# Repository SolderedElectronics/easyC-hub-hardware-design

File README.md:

# easyC Hub Hardware design

## About the product

|  |
| :----------------------------------------------------------: |
|      [Buy easyC Hub](https://www.solde.red/333018)      |

We made the easyC system for faster prototyping and easy connection between the components. However, some of the components have only one easyC port or you just want your cable managmenet made better. What to do in those cases? The easyC hub comes to the rescue! It has six connectors so you can easily expand your circuit. It’s as simple of a device as it can get.

## Repository contents

All Soldered Electronics hardware designed in KiCAD, and repositories are organized in the following way:

- CAD folder - contains KiCAD files (Schematics, Board, Panel Board), sorted by version. Change log lists all changes between versions.
- OUTPUTS - contains useful files, such as Bill of Materials (BOM), PDF of schematics, 3D .step file of the board and gerber files, sorted by version. 
- OUTPUTS -> Compliance - Certificates and useful legal stuff. 

## Want to contribute?

Please feel free to submit a pull request if you have any contributions. We encourage you to submit an issue or pull request if you find a bug. 

## About Soldered

At Soldered, we design and manufacture a wide selection of electronic products to help you turn your ideas into acts and bring you one step closer to your final project. Our products are intented for makers and crafted in-house by our experienced team in Osijek, Croatia. We believe that sharing is a crucial element for improvement and innovation, and we work hard to stay connected with all our makers regardless of their skill or experience level. Therefore, all our products are open-source. Finally, we always have your back. If you face any problem concerning either your shopping experience or your electronics project, our team will help you deal with it, offering efficient customer service and cost-free technical support anytime. Some of those might be useful for you:

- [Web Store](https://www.soldered.com/shop)
- [Tutorials & Projects](https://soldered.com/learn)
- [Community & Technical support](https://soldered.com/community)

## License info

All Soldered open-source hardware (OSH) is under The TAPR Open Hardware License. Read more in the LICENSE file. 

No warranty - all designs in this repository are distributed in the hope that they will be useful, but without any warranty. They are provided "AS IS", therefore without warranty of any kind, either expressed or implied. The entire quality and performance of what you do with the contents of this repository are your responsibility. In no event, Soldered Electronics will be liable for your damages, losses, including any general, special, incidental or consequential damage arising out of the use or inability to use the contents of this repository. 

## Have fun! 
And thank you from your fellow makers at Soldered Electronics.

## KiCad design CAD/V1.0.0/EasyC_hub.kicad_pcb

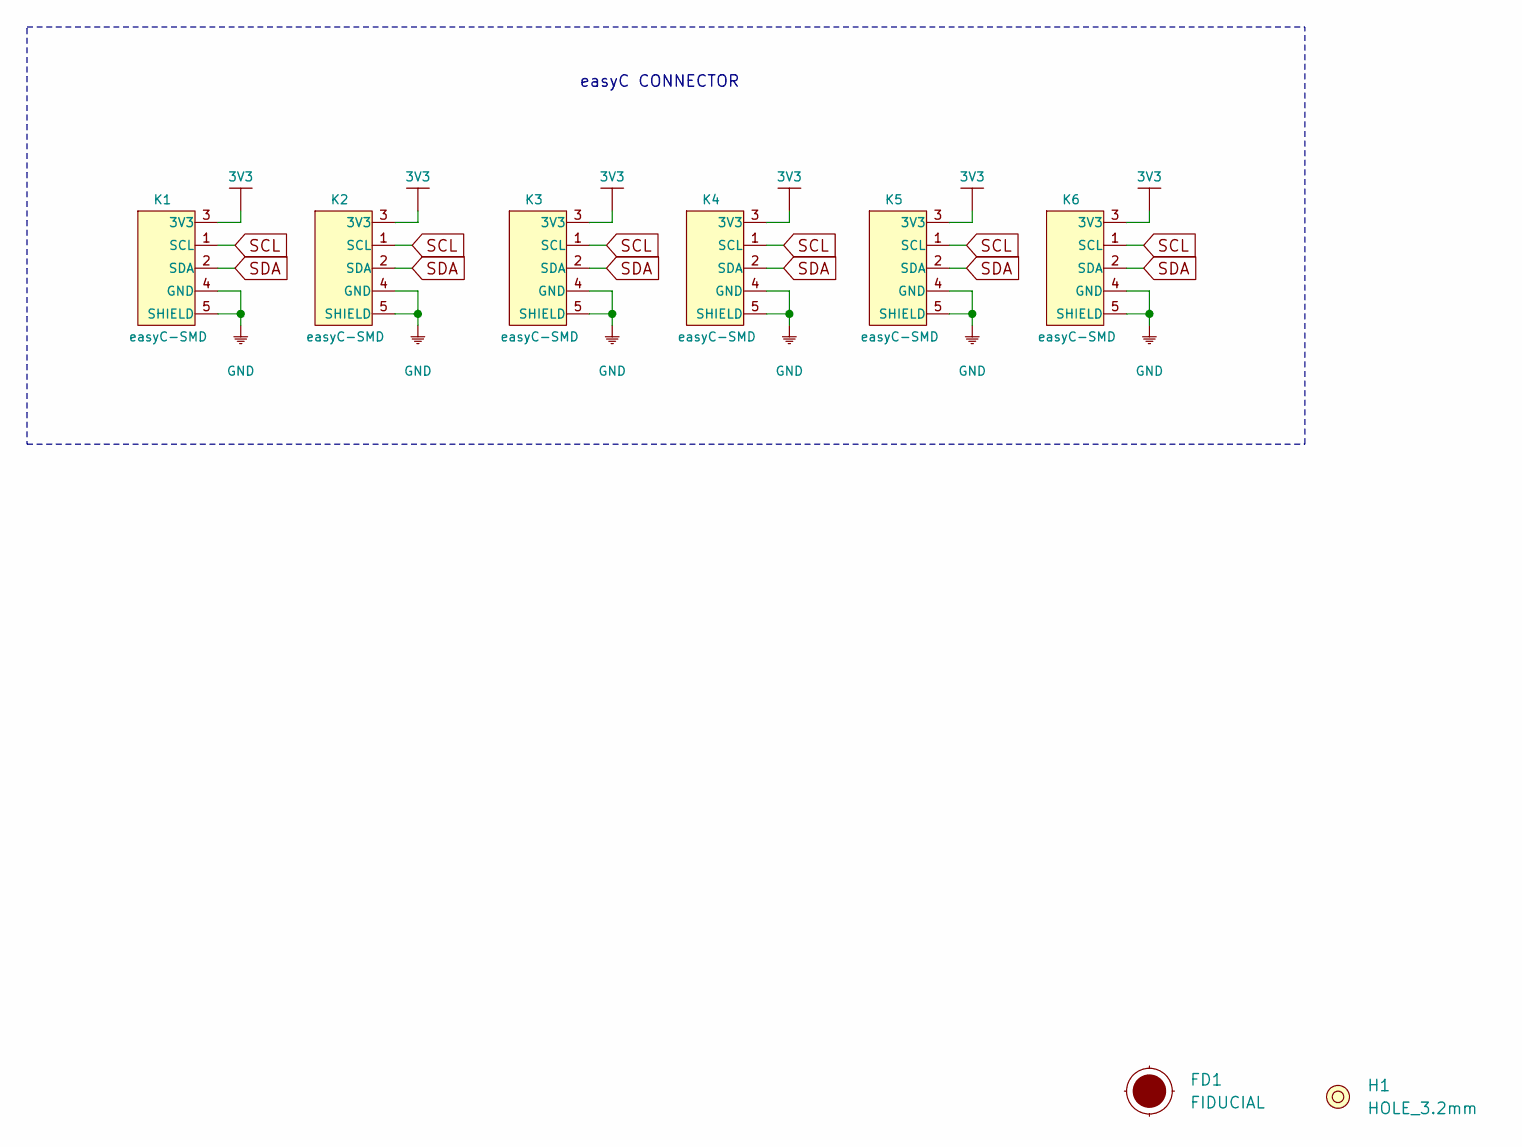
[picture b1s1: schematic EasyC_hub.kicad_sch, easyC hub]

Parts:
FD1: FIDUCIAL; FIDUCIAL_23
H1: HOLE_3.2mm
K1, K2, K3, K4, K5, K6: easyC-SMD; easyC-connector

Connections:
3V3: K1.3 (3V3), K2.3 (3V3), K3.3 (3V3), K4.3 (3V3), K5.3 (3V3), K6.3 (3V3)
GND: K1.4 (GND), K1.5 (SHIELD), K2.4 (GND), K2.5 (SHIELD), K3.4 (GND), K3.5 (SHIELD), K4.4 (GND), K4.5 (SHIELD), K5.4 (GND), K5.5 (SHIELD), K6.4 (GND), K6.5 (SHIELD)
SCL: K1.1 (SCL), K2.1 (SCL), K3.1 (SCL), K4.1 (SCL), K5.1 (SCL), K6.1 (SCL)
SDA: K1.2 (SDA), K2.2 (SDA), K3.2 (SDA), K4.2 (SDA), K5.2 (SDA), K6.2 (SDA)

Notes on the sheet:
easyC CONNECTOR

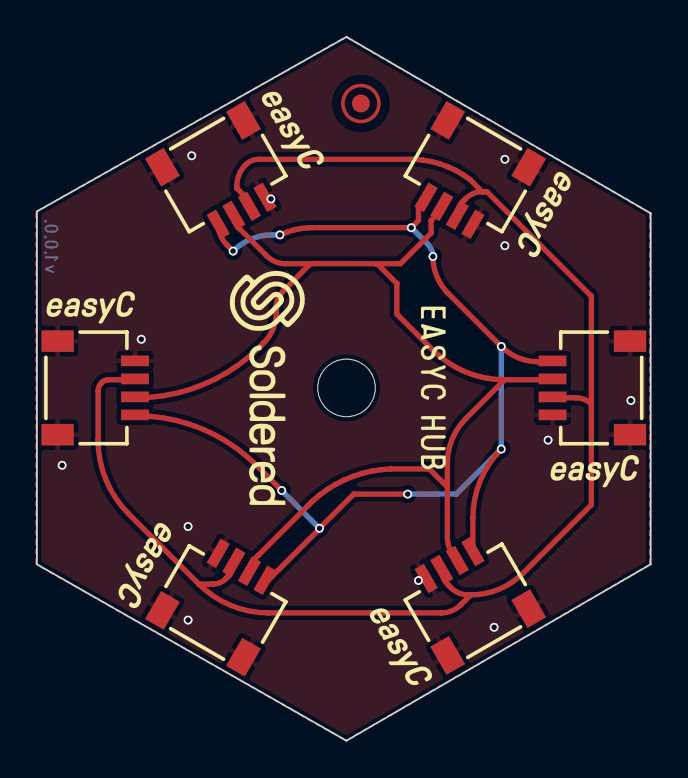
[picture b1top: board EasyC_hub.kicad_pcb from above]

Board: 2 copper layers, 34.1 x 39.1 mm, 9 parts (1 on the bottom side), 4 nets.

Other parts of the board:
Ref**: Val**; Version1.0.0.

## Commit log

2022-08-06 Updating open source files.
